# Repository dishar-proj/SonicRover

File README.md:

# Sonic Rover
Contributors: Disha Rachur, Emerson Hall, Zane Bush, Garv Bhumbla, Navangana Jha
Components: Raspberry Pi, H-Bridge, Motors, Chebychev Filters, Python

User Manual: https://dr43632.wixsite.com/my-site-3

The main objective of this project is to design a car that can detect and move to multiple fixed audio frequencies. Each team received a kit of parts to build an audio car. The design should prioritize cost-effective solutions to minimize financial strain. The team is free to utilize parts they buy with their own budget, however, if any component burns or gets damaged, the team is responsible for providing and paying for a new one. 

The design team is composed of five members. Garv Bhumbla (EE) is responsible for the hardware, power supply, and wiring components.  Zane Bush (EE) is responsible for operating the RP4 and looking over hardware to check functionality. Emerson Hall (CSE) is responsible for writing and debugging code, and monitoring the ADC. Navangana Jha (CSE) is responsible for checking and modifying the code if issues arise, and helps with documentation. Disha Rachur (CSE) is responsible for task organization, documentation, and some wiring. 

This project is organized into three major checkpoints. The first checkpoint requires the car to travel along a straight line path, square path, and a figure eight path. The second checkpoint consists of the car detecting the C8 frequency, moving towards it, and stopping. The final checkpoint requires the car to detect and move towards the C8 frequency and then detect the and move towards the C6 frequency. The first checkpoint is the minimum for a C, the second checkpoint is the minimum required for a B, and the third checkpoint is the minimum for an A-. Each week, teams will be assigned a progress deliverable or a design deliverable to add and refine the functionality of the audio car. The weekly tasks ensure that the group is able to work collaboratively toward project goals.

In addition to technical development, the project emphasizes teamwork and collaboration. CATME surveys were conducted throughout the duration of the project to assess team dynamics, address team issues, and enhance team efficiency.

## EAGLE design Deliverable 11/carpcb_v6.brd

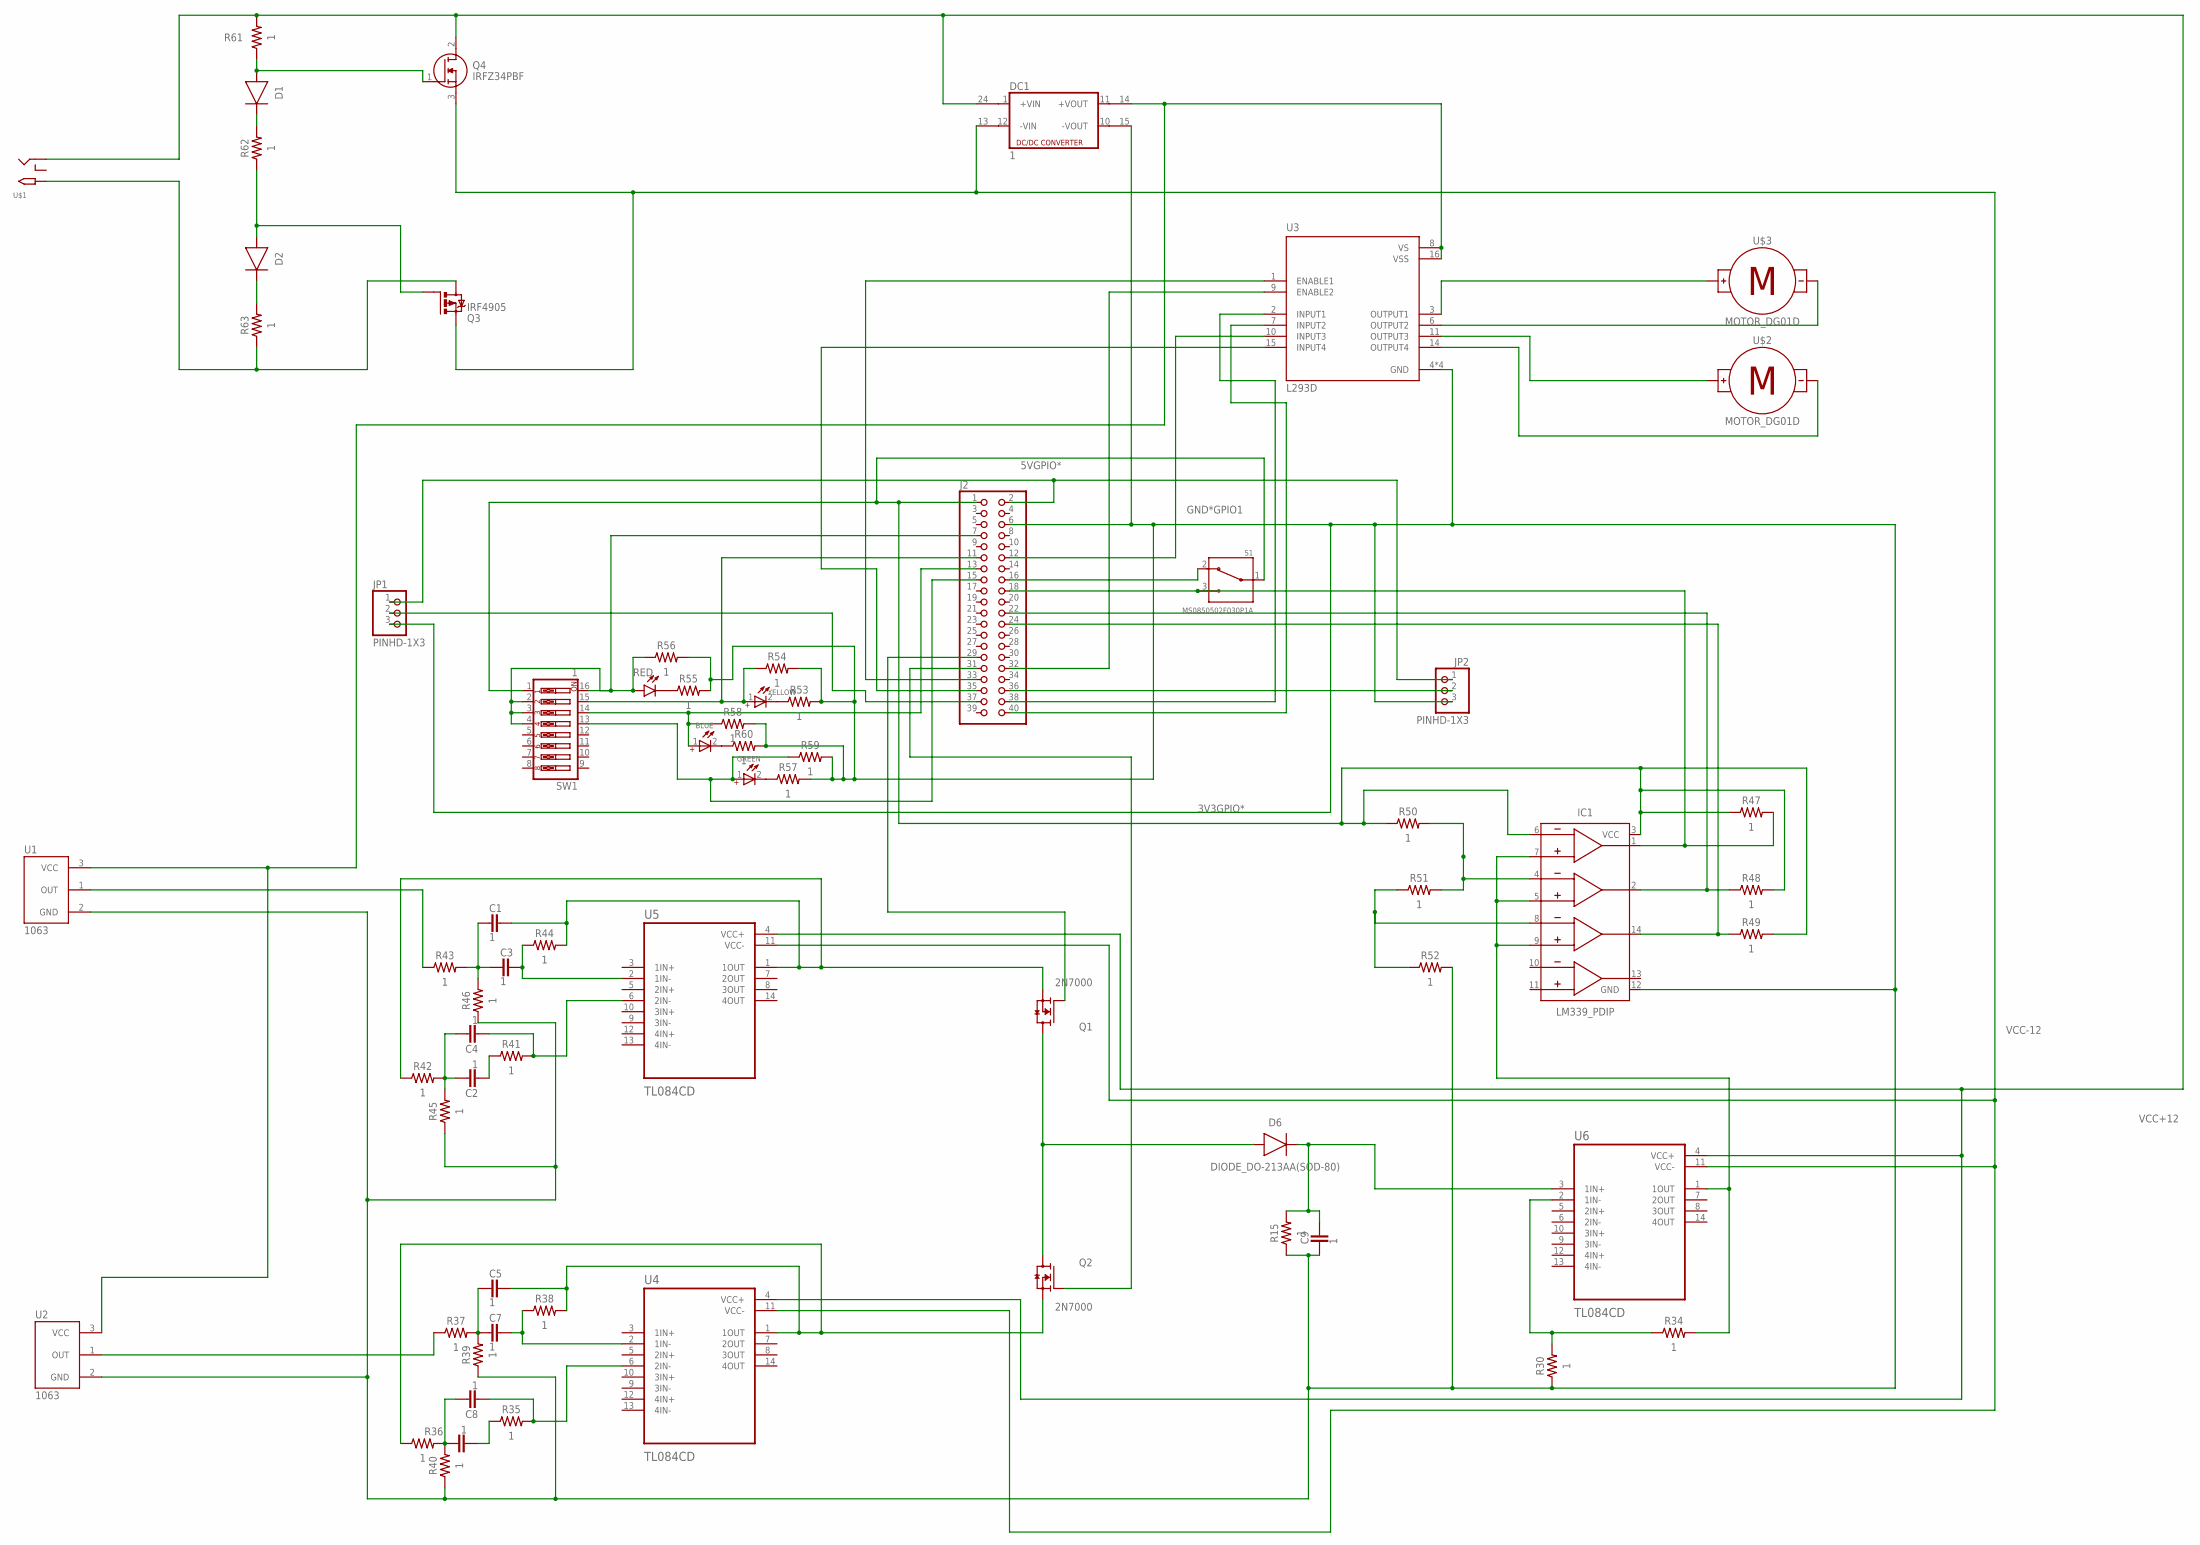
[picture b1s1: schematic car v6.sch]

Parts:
BLUE: WL-TMRC_5MM_WITHOUTSTOPPER; WL-TMRC_5MM
C1, C2, C3, C4, C5, C6, C7, C8, C9: 1; CAPC1005X60
D1, D2, D6: DIODE_DO-213AA(SOD-80); DIOMELF3516
DC1: 1; CMK
GREEN: WL-TMRC_3MM_WITHOUTSTOPPER; WL-TMRC_3MM
IC1: LM339_PDIP; DIP762W53P254L1969H508Q14B
J2: PiHeaderM; 2X20
JP1, JP2: PINHD-1X3; 1X03
Q1, Q2: 2N7000; TO92254P458H750-3
Q3: IRF4905; TO220BH
Q4: IRFZ34PBF; TO254P465X1024X2050-3P
R15, R30, R34, R35, R36, R37, R38, R39, R40, R41, R42, R43, R44, R45, R46, R47, R48, R49, R50, R51, R52, R53, R54, R55, R56, R57, R58, R59, R60, R61, R62, R63: 1; RESC1005X40
RED: LED_RADIALRED; LEDRD254W60D565H860B_R
S1: MS0850502F030P1A; SW_MS0850502F030P1A
SW1: 1; EDG-08
U1, U2: 1063; MODULE_1063
U3: L293D; DIP880W50P254L2000H510Q16
U4, U5, U6: TL084CD; SOIC127P600X175-14N
U$1: 2.1MMJACKTHM; PJ-102A
U$2, U$3: MOTOR_DG01D; DG01D
YELLOW: WL-TMRC_3MM_WITHOUTSTOPPER; WL-TMRC_3MM

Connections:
3V3GPIO*: IC1.3 (VCC), IC1.6 (-IN1), J2.1, R47.1, R48.2, R49.2, R50.1, S1.1 (COM), SW1.1
5VGPIO*: J2.2, JP1.1, JP2.1
GND*GPIO1: C9.2, DC1.15 (-VOUT1), IC1.12 (GND), J2.6, JP1.3, JP2.3, R15.1, R30.1, R39.1, R40.1, R45.1, R46.1, R52.2, R53.2, R54.2, R55.2, R56.2, R57.2, R58.2, R59.2, R60.2, U1.2 (GND), U2.2 (GND), U3.4 (GND), U3.5 (GND), U3.12 (GND), U3.13 (GND)
GPIO4*: J2.7, R56.1, RED.A, SW1.2, SW1.3, SW1.4, SW1.16
GPIO5*: J2.29, Q1.2 (G)
GPIO6*: J2.31, Q2.2 (G)
GPIO8*: IC1.14 (OUT3), J2.24, R49.1
GPIO12*: J2.32, U3.9 (ENABLE2)
GPIO13*: J2.33, U3.1 (ENABLE1)
GPIO16*: J2.36, JP2.2
GPIO17*: J2.11, R54.1, SW1.15, YELLOW.1 (+)
GPIO18*: J2.12, U3.10 (INPUT3)
GPIO19*: J2.35, U3.15 (INPUT4)
GPIO20*: J2.38, U3.2 (INPUT1)
GPIO21*: J2.40, U3.7 (INPUT2)
GPIO22*: GREEN.1 (+), J2.15, R59.1, SW1.13
GPIO23*: J2.16, S1.2 (NC)
GPIO24*: IC1.1 (OUT1), J2.18, R47.2, S1.3 (NO)
GPIO25*: IC1.2 (OUT2), J2.22, R48.1
GPIO26*: J2.37, JP1.2
GPIO27*: BLUE.1 (+), J2.13, R58.1, SW1.14
unnamed: D1.2 (A), Q4.1 (G), R61.1
unnamed: D1.1 (C), R62.2
unnamed: D2.2 (A), Q3.G, R62.1
unnamed: D2.1 (C), R63.2
unnamed: Q3.D, R63.1, U$1.TIP
unnamed: U3.11 (OUTPUT3), U$2.+
unnamed: U3.3 (OUTPUT1), U$3.+
unnamed: C1.2, C3.2, R43.2, R46.2
unnamed: DC1.14 (+VOUT1), U1.3 (VCC), U2.3 (VCC), U3.8 (VS), U3.16 (VSS)
unnamed: C3.1, R44.1, U5.2 (1IN-)
unnamed: C2.1, C4.1, R42.2, R45.2
unnamed: C2.2, R41.1
unnamed: C1.1, Q1.1 (S), R42.1, R44.2, U5.1 (1OUT)
unnamed: C4.2, R41.2, U5.6 (2IN-)
unnamed: R55.1, RED.C
unnamed: R43.1, U1.1 (OUT)
unnamed: C5.2, C7.2, R37.2, R39.2
unnamed: C7.1, R38.1, U4.2 (1IN-)
unnamed: C6.1, C8.1, R36.2, R40.2
unnamed: C6.2, R35.1
unnamed: C5.1, Q2.1 (S), R36.1, R38.2, U4.1 (1OUT)
unnamed: C8.2, R35.2, U4.6 (2IN-)
unnamed: R53.1, YELLOW.2 (-)
unnamed: R37.1, U2.1 (OUT)
unnamed: C9.1, D6.1 (C), R15.2, U6.3 (1IN+)
unnamed: GREEN.2 (-), R57.1
unnamed: D6.2 (A), Q1.3 (D), Q2.3 (D)
unnamed: BLUE.2 (-), R60.1
unnamed: IC1.4 (-IN2), R50.2, R51.2
unnamed: IC1.8 (-IN3), R51.1, R52.1
unnamed: U3.6 (OUTPUT2), U$3.-
unnamed: R30.2, R34.1, U6.2 (1IN-)
unnamed: IC1.5 (+IN2), IC1.7 (+IN1), IC1.9 (+IN3), R34.2, U6.1 (1OUT)
unnamed: U3.14 (OUTPUT4), U$2.-
VCC+12: DC1.24 (+VIN1), Q4.2 (D), R61.2, U4.4 (VCC+), U5.4 (VCC+), U6.4 (VCC+), U$1.RING
VCC-12: DC1.13 (-VIN1), Q3.S, Q4.3 (S), U4.11 (VCC-), U5.11 (VCC-), U6.11 (VCC-)

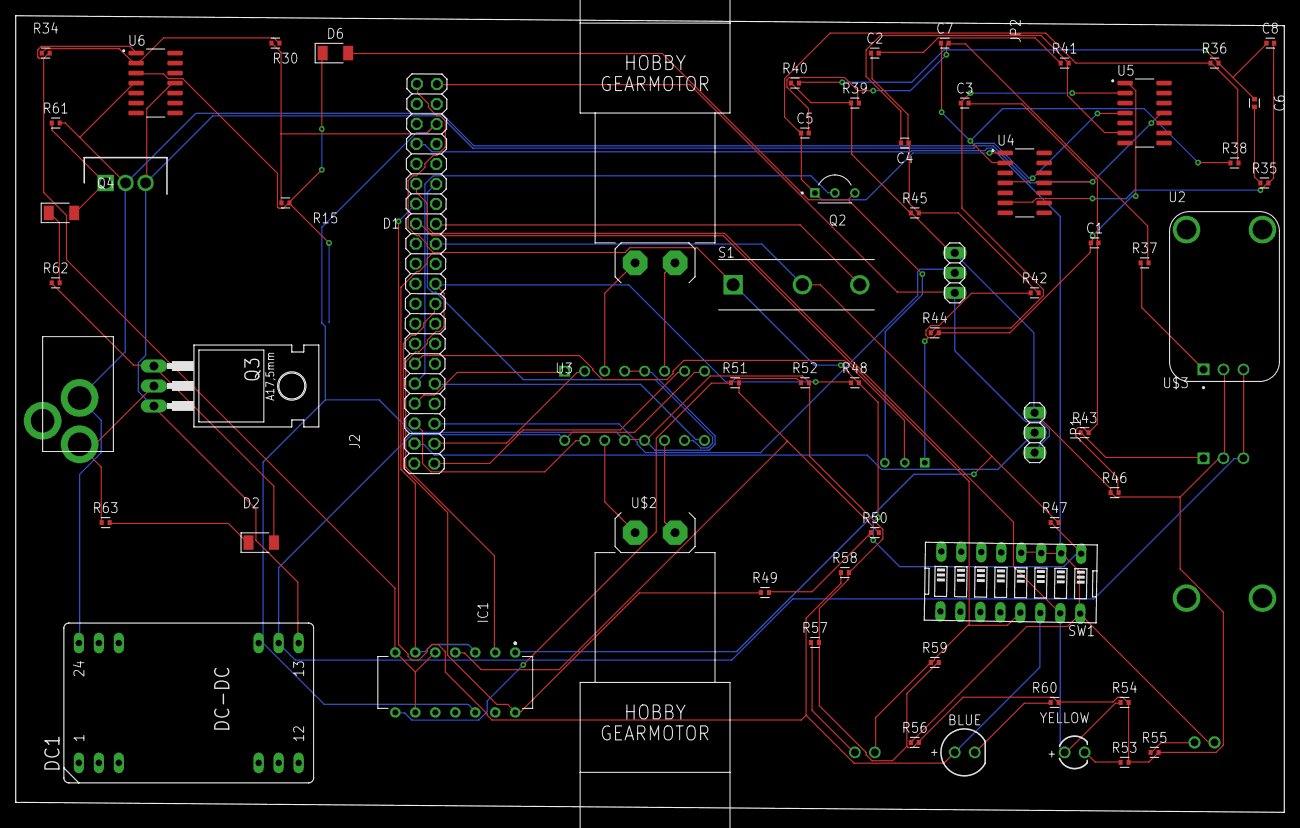
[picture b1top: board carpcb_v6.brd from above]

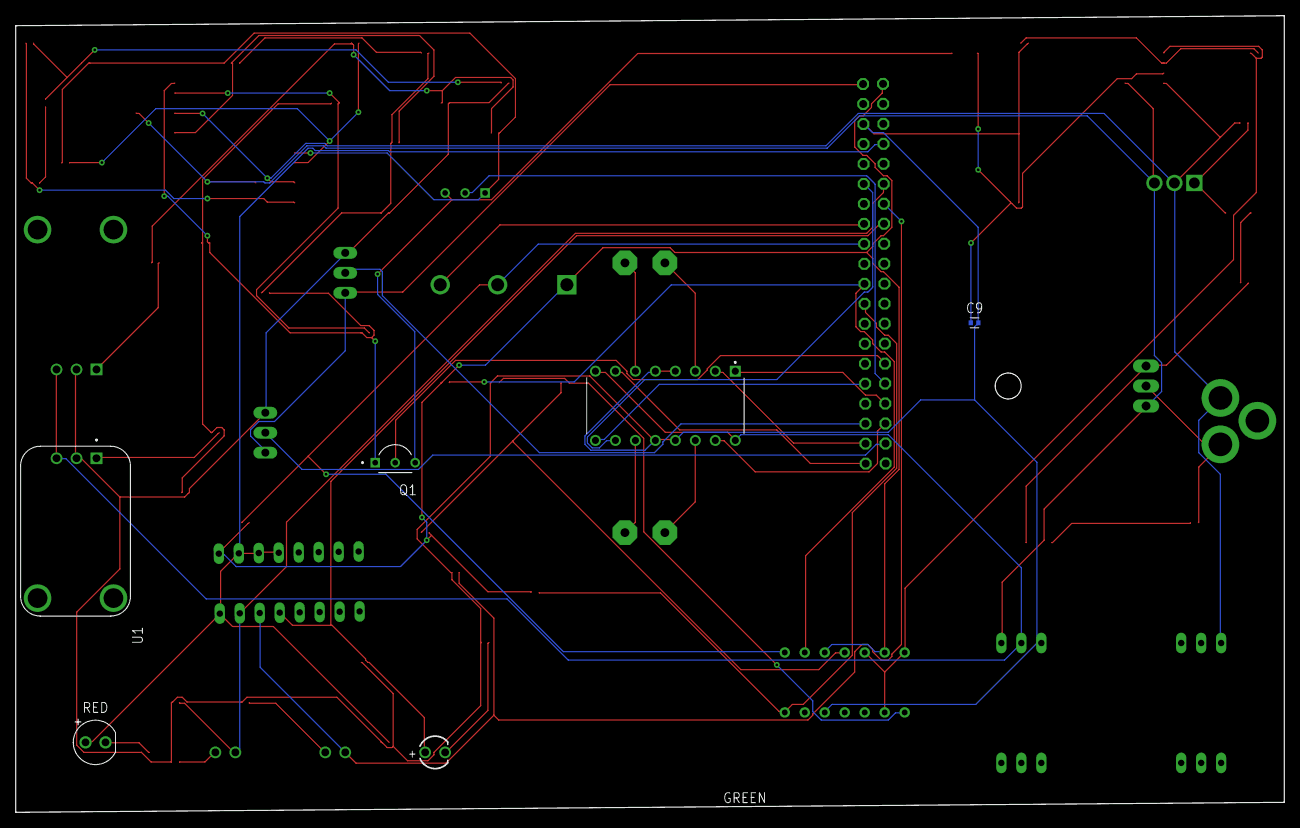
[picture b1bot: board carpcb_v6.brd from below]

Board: 2 copper layers, 161.3 x 101.3 mm, 68 parts (6 on the bottom side), 57 nets.
